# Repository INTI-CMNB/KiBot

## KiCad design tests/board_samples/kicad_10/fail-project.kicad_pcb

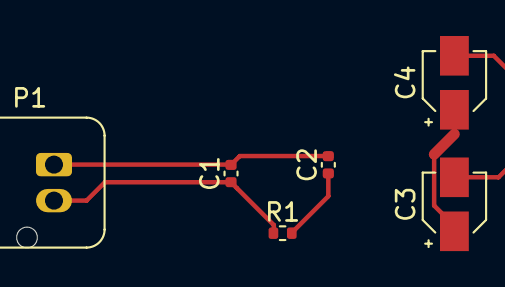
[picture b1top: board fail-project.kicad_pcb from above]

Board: 2 copper layers, 6 parts (0 on the bottom side), 5 nets.

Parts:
C1, C2: C; C_0402_1005Metric
C3, C4: CP; CP_Elec_3x5.3
P1: CONN_01X02; JST_JWPF_B02B-JWPF-SK-R_1x02_P2.00mm_Vertical
R1: R; R_0402_1005Metric

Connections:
/Power/VCC: C1.1, P1.2, R1.1
GND: C1.2, C2.2, P1.1
unnamed: C2.1, R1.2
unnamed: C3.1, C4.1
unnamed: C3.2, C4.2

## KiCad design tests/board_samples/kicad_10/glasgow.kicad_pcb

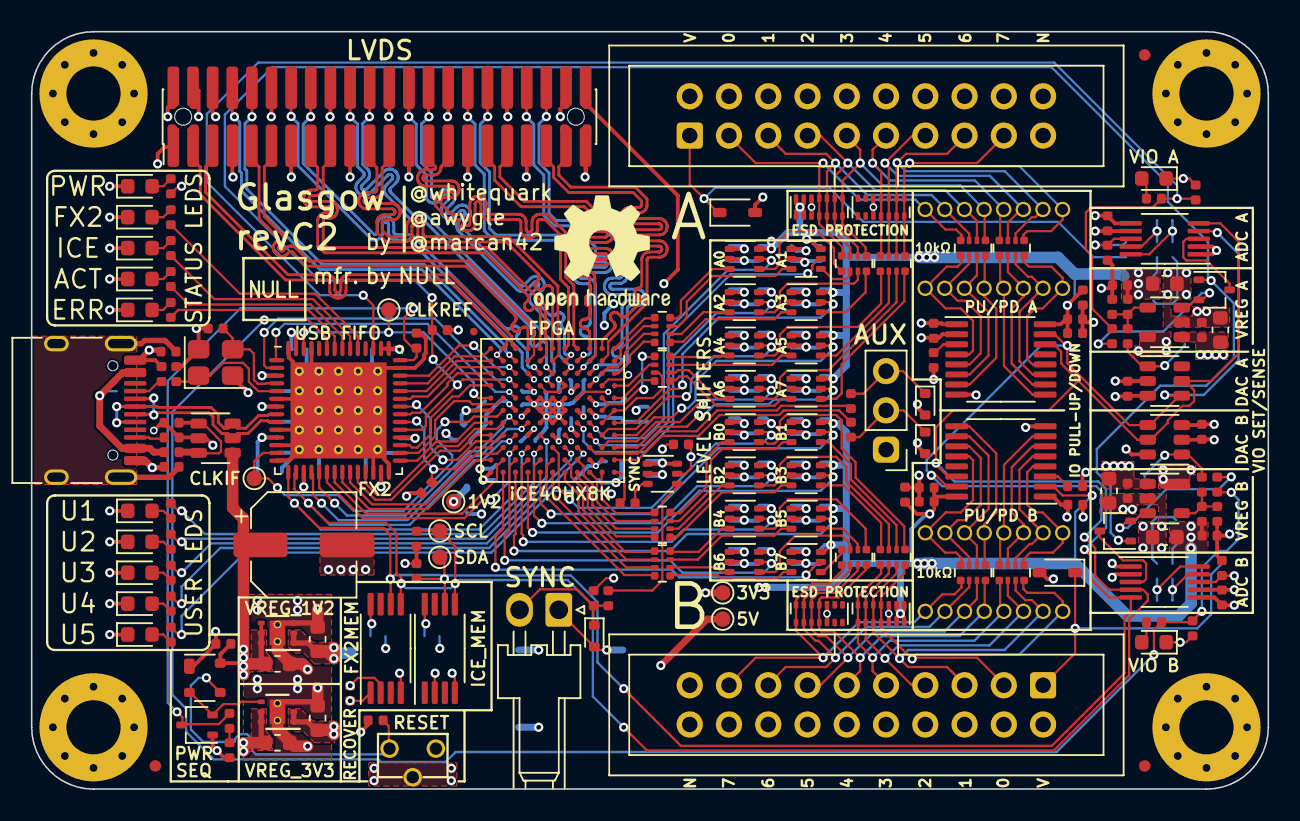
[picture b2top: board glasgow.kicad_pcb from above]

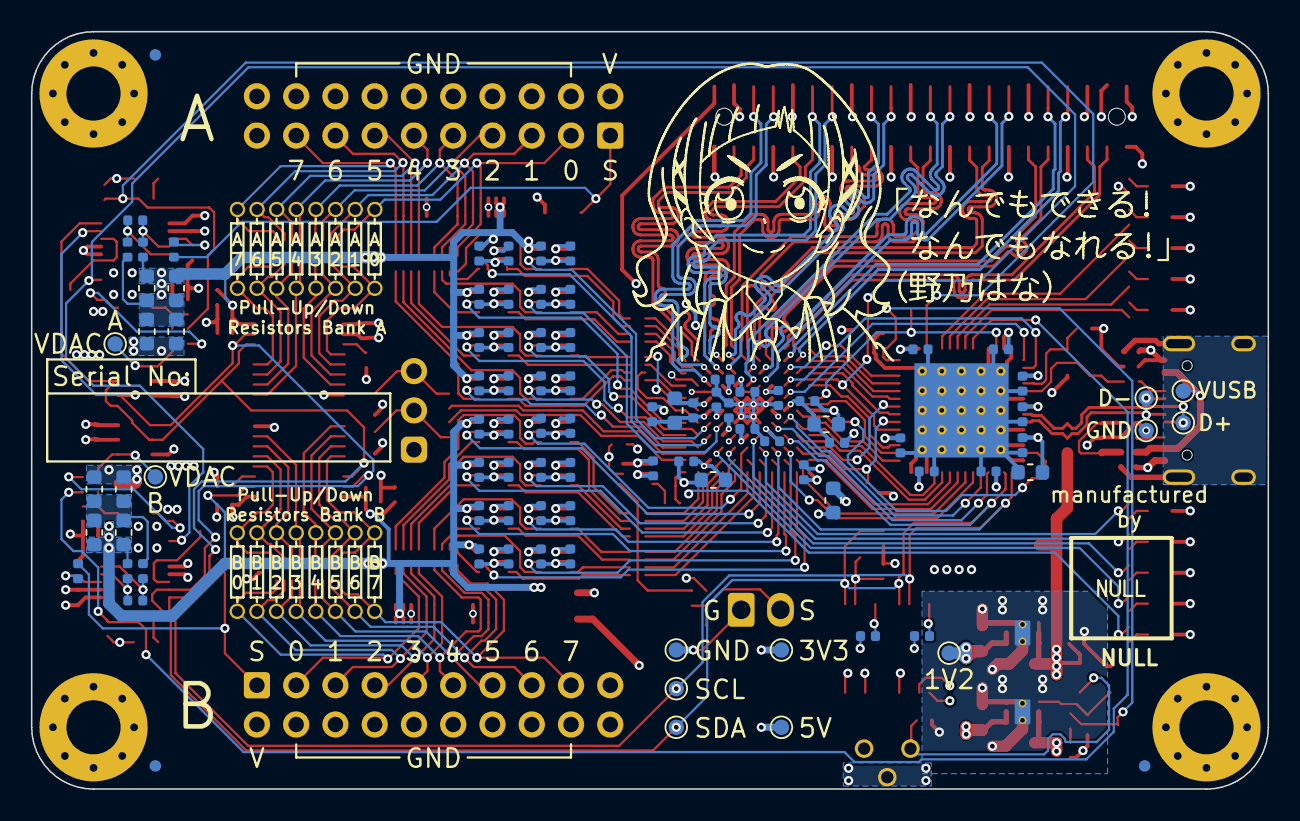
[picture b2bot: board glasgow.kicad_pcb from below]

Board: 4 copper layers, 80.0 x 49.0 mm, 264 parts (93 on the bottom side), 226 nets.

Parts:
C1, C14, C19, C26, C27, C28, C31, C53, C76, C80, C82, C83, C86: 4u7; C_0603_1608Metric
C2, C3, C4, C5, C6, C7, C8, C9, C10, C13, C15, C16, C17, C18, C20, C21, C22, C23, C24, C25, C29, C30, C32, C33, C34, C35, C36, C37, C38, C39, C40, C41, C42, C43, C44, C45, C46, C47, C48, C49, C50, C51, C52, C54, C55, C56, C57, C58, C59, C60, C61, C62, C63, C64, C65, C66, C67, C68, C69, C70, C71, C72, C73, C74, C75, C77, C78, C79, C81, C84, C85, C88, C89: u1; C_0402_1005Metric
C11, C12: 9p; C_0402_1005Metric
C87: 150u; CP_Elec_6.3x5.9
C90, C91: DNP; C_0402_1005Metric_DNP
D1, D2, D3, D14, D15: GRN; LED_0603_1608Metric
D4: YEL; LED_0603_1608Metric
D5: RED; LED_0603_1608Metric
D6, D10: BLU; LED_0603_1608Metric
D7, D9: PNK; LED_0603_1608Metric
D8: WHT; LED_0603_1608Metric
D11, D12, D13: ESD5Z5.0T1G; D_SOD-523
D16, D17: CDSOD323-T36S; D_SOD-323
D18, D19: BAT54CW; SOT-323_SC-70
D20, D21, D22, D23: SP3012-06UTG; UDFN-14_3.5x1.35mm_P0.5mm
D24: BAT54AW; SOT-323_SC-70
FB1: 600R, 0.5A; L_0402_1005Metric
FID1, FID2, FID3, FID4, FID5, FID6: Fiducial_0.75mm_Mask1.5mm
FID8: Fiducial_0.5mm_Dia_1mm_Outer
J1: USB_C_USB2.0; USB_C_Receptacle_HRO_TYPE-C-31-M-12
J2, J3: IDC-Header_2x10_P2.54mm; IDC-Header_2x10_P2.54mm_Vertical
J4: Conn_01x02; Molex_KK-254_1x02_P2.54mm_Horizontal
J5: PinHeader_2x22_P1.27mm; PinHeader_2x22_P1.27mm_Vertical__SMD
J6, J7, J8, J9: Conn_01x08; PinSocket_1x08_P1.27mm_Vertical_DNP
J10: AUX; PinHeader_1x03_P2.54mm_Vertical
MK1, MK2, MK3, MK4: Mounting_Hole_PAD; MountingHole_3.5mm_Pad_Via_CrtYd
NONO_HANA: MECHOKKU; nono_hana_lines
R1, R2, R10, R15, R41, R42, R57, R58: 2k2; R_0402_1005Metric
R3, R4, R5, R9, R17: 100k; R_0402_1005Metric
R6, R8, R50, R51: DNP; R_0603_1608Metric_DNP
R7, R56: 0R33; R_0603_1608Metric
R11, R23: 4k7; R_0402_1005Metric
R12, R13, R14, R46, R47: 20k; R_0402_1005Metric
R16, R18, R19, R20, R22, R26, R36, R37, R44, R55: 10k; R_0402_1005Metric
R21: 6k8; R_0402_1005Metric
R24, R25, R30, R54, R59, R60: 4R7; R_0402_1005Metric
R27, R33: 49k9; R_0402_1005Metric
R28, R34: 59k; R_0402_1005Metric
R29, R35: 24k3; R_0402_1005Metric
R31, R32: 100R; R_0402_1005Metric
R38, R39, R43, R45: 47R; R_0402_1005Metric
R40: DNP; R_0402_1005Metric_DNP
R48, R49: 0R15; R_0603_1608Metric
R52, R53: 5k1; R_0402_1005Metric
RN1, RN2, RN3, RN4, RN7, RN8, RN9, RN10: 33R; R_Array_Convex_4x0402
RN5, RN6, RN11, RN12: 10k; R_Array_Convex_4x0402
SW1: RST; SW_Tactile_SPST_Angled_TC-1109DE
TP1, TP8: 5V; TestPoint_Pad_D1.0mm
TP2, TP17: 1V2; TestPoint_Pad_D1.0mm
TP3, TP7, TP9: 3V3; TestPoint_Pad_D1.0mm
TP4, TP10: SDA; TestPoint_Pad_D1.0mm
TP5, TP11: SCL; TestPoint_Pad_D1.0mm
TP6: CLKREF; TestPoint_Pad_D1.0mm
TP12: GND; TestPoint_Pad_D1.0mm
TP13: VBUS; TestPoint_Pad_D1.0mm
TP14: USBGND; TestPoint_Pad_D1.0mm
TP15: USBDP; TestPoint_Pad_D1.0mm
TP16: USBDM; TestPoint_Pad_D1.0mm
TP18, TP19: VDAC; TestPoint_Pad_D1.0mm
U1: CY7C68013A-56LTX; Cypress_QFN-56-1EP_8x8mm_P0.5mm_EP6.22x6.22mm_ThermalVias
U2: CAT24M01X; TSSOP-8_4.4x3mm_P0.65mm
U3: BL24C256A-SFRC; TSSOP-8_4.4x3mm_P0.65mm
U4, U6, U9, U10, U11, U16, U17, U18, U22, U23, U24, U25, U26, U27, U28, U29, U32: SN74LVC1T45DCKR; SOT-363_SC-70-6
U5, U19: PCA6408APW; TSSOP-16_4.4x5mm_P0.65mm
U7: APX811-40UG-7; SOT-143
U8: TLV75533PDRVR; DFN-6-1EP_2x2mm_P0.65mm_EP1x1.6mm_ThermalVias
U12, U21: INA233; VSSOP-10_3x3mm_P0.5mm
U13, U20: DAC081C081CIMK; SOT-23-6
U14, U31: TPS73101DBV; SOT-23-5
U15: TPD3S014; SOT-23-6
U30: ICE40HX8K-BG121; BGA-121_9.0x9.0mm_Layout11x11_P0.8mm_Ball0.4mm_Pad0.35mm_NS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
U36: TLV73312PQDRVR; DFN-6-1EP_2x2mm_P0.65mm_EP1x1.6mm_ThermalVias
Y1: 24M; Crystal_SMD_3225-4Pin_3.2x2.5mm

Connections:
+1V2: C14.1, C18.1, C24.1, C25.1, C27.1, C77.1, R31.2, R32.2, TP2.1, TP17.1, U30.D4, U30.D8, U30.H4, U30.H8, U36.1, U36.2
+3V3: C1.1, C2.1, C3.1, C4.1, C5.1, C6.1, C7.1, C9.1, C10.1, C15.1, C17.1, C19.1, C20.1, C21.1, C22.1, C23.1, C28.1, C30.1, C32.1, C34.1, C35.1, C36.1, C37.1, C42.1, C43.1, C47.1, C48.1, C55.1, C56.1, C60.1, C61.1, C62.1, C63.1, C68.1, C69.1, C70.1, C71.1, C81.1, C84.1, C85.1, D24.1, J5.2, R1.2, R2.2, R4.1, R12.1, R17.2, R36.2, R37.2, R40.2, R44.2, TP3.1, TP9.1, U1.3, U1.7, U1.11, U1.17, U1.27, U1.32, U1.43, U1.44, U1.55, U2.2, U2.8, U3.1, U3.8, U4.1, U5.1, U6.1, U8.1, U8.2, U9.1, U10.1, U11.1, U12.2, U12.6, U13.2, U16.1, U17.1, U18.1, U19.1, U20.2, U21.6, U22.1, U23.1, U24.1, U25.1, U26.1, U27.1, U28.1, U29.1, U30.C10, U30.D6, U30.F8, U30.H6, U30.L11, U32.1, U32.6
+5V: C16.1, C26.2, C31.1, C45.1, C59.1, C82.1, C86.2, C87.1, TP1.1, TP8.1, U7.4, U8.5, U8.6, U14.1, U15.4, U31.1, U36.4, U36.5, U36.6
/A0: U1.37, U30.K3
/A1: U1.38, U30.L2
/CC1: J1.A5, R53.2
/CC2: J1.B5, R52.2
/CLKIF: TP7.1, U1.13, U30.K6
/CLKREF: TP6.1, U1.54, U30.D5, U30.L5
/D0: U1.18, U30.H7
/D1: U1.19, U30.J7
/D2: U1.20, U30.J9
/D3: U1.21, U30.K10
/D4: U1.22, U30.L10
/D5: U1.23, U30.K9
/D6: U1.24, U30.L8
/D7: U1.25, U30.K7
/ENVA: R18.1, R47.1, R55.2, U1.45
/ENVB: R19.1, R26.2, R46.1, U1.51
/FLAGA: U1.29, U30.L7
/FLAGB: U1.30, U30.K5
/FLAGC: U1.31, U30.L4
/FLAGD: U1.40, U30.J3
/FPGA_DONE: U1.36, U30.K8
/GNDPLL0: C76.2, C78.2, U30.L6
/GNDPLL1: C79.2, C80.2, U30.C5
/IO_Banks/DA0: U4.5, U30.C7
/IO_Banks/DA1: U11.5, U30.C8
/IO_Banks/DA2: U6.5, U30.D7
/IO_Banks/DA3: U16.5, U30.A7
/IO_Banks/DA4: U9.5, U30.B8
/IO_Banks/DA5: U17.5, U30.A8
/IO_Banks/DA6: U10.5, U30.B9
/IO_Banks/DA7: U18.5, U30.A9
/IO_Banks/DB0: U22.5, U30.F9
/IO_Banks/DB1: U26.5, U30.G11
/IO_Banks/DB2: U23.5, U30.G10
/IO_Banks/DB3: U27.5, U30.H11
/IO_Banks/DB4: U24.5, U30.H10
/IO_Banks/DB5: U28.5, U30.J11
/IO_Banks/DB6: U25.5, U30.J10
/IO_Banks/DB7: U29.5, U30.K11
/IO_Banks/IO_Buffer_A/ISNS_H: R8.2, R30.1, R49.1, R51.1, R56.2
/IO_Banks/IO_Buffer_A/P0: J9.1, RN11.5, U19.4
/IO_Banks/IO_Buffer_A/P1: J9.2, RN11.6, U19.5
/IO_Banks/IO_Buffer_A/P2: J9.3, RN11.7, U19.6
/IO_Banks/IO_Buffer_A/P3: J9.4, RN11.8, U19.7
/IO_Banks/IO_Buffer_A/P4: J9.5, RN12.5, U19.9
/IO_Banks/IO_Buffer_A/P5: J9.6, RN12.6, U19.10
/IO_Banks/IO_Buffer_A/P6: J9.7, RN12.7, U19.11
/IO_Banks/IO_Buffer_A/P7: J9.8, RN12.8, U19.12
/IO_Banks/IO_Buffer_A/VDAC: R33.1, TP19.1, U20.1
/IO_Banks/IO_Buffer_A/VFB: R33.2, R34.1, R35.2, U31.4
/IO_Banks/IO_Buffer_A/VIO_EN: D19.2, R55.1, U31.3
/IO_Banks/IO_Buffer_A/VSENSE: D17.1, J2.1, R60.2
/IO_Banks/IO_Buffer_A/X0: RN7.8, U4.3
/IO_Banks/IO_Buffer_A/Y0: RN9.1, U4.4
/IO_Banks/IO_Buffer_A/Y1: RN9.2, U11.4
/IO_Banks/IO_Buffer_A/Y2: RN9.3, U6.4
/IO_Banks/IO_Buffer_A/Y3: RN9.4, U16.4
/IO_Banks/IO_Buffer_A/Y4: RN10.1, U9.4
/IO_Banks/IO_Buffer_A/Y5: RN10.2, U17.4
/IO_Banks/IO_Buffer_A/Y6: RN10.3, U10.4
/IO_Banks/IO_Buffer_A/Y7: RN10.4, U18.4
/IO_Banks/IO_Buffer_A/Z0: D22.4, D22.11, J2.3, J8.1, RN9.8, RN11.4
/IO_Banks/IO_Buffer_A/Z1: D22.3, D22.12, J2.5, J8.2, RN9.7, RN11.3
/IO_Banks/IO_Buffer_A/Z2: D22.2, D22.13, J2.7, J8.3, RN9.6, RN11.2
/IO_Banks/IO_Buffer_A/Z3: D22.1, D22.14, J2.9, J8.4, RN9.5, RN11.1
/IO_Banks/IO_Buffer_A/Z4: D23.4, D23.11, J2.11, J8.5, RN10.8, RN12.4
/IO_Banks/IO_Buffer_A/Z5: D23.3, D23.12, J2.13, J8.6, RN10.7, RN12.3
/IO_Banks/IO_Buffer_A/Z6: D23.2, D23.13, J2.15, J8.7, RN10.6, RN12.2
/IO_Banks/IO_Buffer_A/Z7: D23.1, D23.14, J2.17, J8.8, RN10.5, RN12.1
/IO_Banks/IO_Buffer_B/ISNS_H: R6.2, R7.2, R24.1, R48.1, R50.1
/IO_Banks/IO_Buffer_B/P0: J7.1, RN5.5, U5.4
/IO_Banks/IO_Buffer_B/P1: J7.2, RN5.6, U5.5
/IO_Banks/IO_Buffer_B/P2: J7.3, RN5.7, U5.6
/IO_Banks/IO_Buffer_B/P3: J7.4, RN5.8, U5.7
/IO_Banks/IO_Buffer_B/P4: J7.5, RN6.5, U5.9
/IO_Banks/IO_Buffer_B/P5: J7.6, RN6.6, U5.10
/IO_Banks/IO_Buffer_B/P6: J7.7, RN6.7, U5.11
/IO_Banks/IO_Buffer_B/P7: J7.8, RN6.8, U5.12
/IO_Banks/IO_Buffer_B/VDAC: R27.1, TP18.1, U13.1
/IO_Banks/IO_Buffer_B/VFB: R27.2, R28.1, R29.2, U14.4
/IO_Banks/IO_Buffer_B/VIO_EN: D18.2, R26.1, U14.3
/IO_Banks/IO_Buffer_B/VSENSE: D16.1, J3.1, R59.2
/IO_Banks/IO_Buffer_B/X0: RN1.8, U22.3
/IO_Banks/IO_Buffer_B/Y0: RN3.1, U22.4
/IO_Banks/IO_Buffer_B/Y1: RN3.2, U26.4
/IO_Banks/IO_Buffer_B/Y2: RN3.3, U23.4
/IO_Banks/IO_Buffer_B/Y3: RN3.4, U27.4
/IO_Banks/IO_Buffer_B/Y4: RN4.1, U24.4
/IO_Banks/IO_Buffer_B/Y5: RN4.2, U28.4
/IO_Banks/IO_Buffer_B/Y6: RN4.3, U25.4
/IO_Banks/IO_Buffer_B/Y7: RN4.4, U29.4
/IO_Banks/IO_Buffer_B/Z0: D20.4, D20.11, J3.3, J6.1, RN3.8, RN5.4
/IO_Banks/IO_Buffer_B/Z1: D20.3, D20.12, J3.5, J6.2, RN3.7, RN5.3
/IO_Banks/IO_Buffer_B/Z2: D20.2, D20.13, J3.7, J6.3, RN3.6, RN5.2
/IO_Banks/IO_Buffer_B/Z3: D20.1, D20.14, J3.9, J6.4, RN3.5, RN5.1
/IO_Banks/IO_Buffer_B/Z4: D21.4, D21.11, J3.11, J6.5, RN4.8, RN6.4
/IO_Banks/IO_Buffer_B/Z5: D21.3, D21.12, J3.13, J6.6, RN4.7, RN6.3
/IO_Banks/IO_Buffer_B/Z6: D21.2, D21.13, J3.15, J6.7, RN4.6, RN6.2
/IO_Banks/IO_Buffer_B/Z7: D21.1, D21.14, J3.17, J6.8, RN4.5, RN6.1
/IO_Banks/QA0: RN7.1, U30.A1
/IO_Banks/QA1: RN7.2, U30.A2
/IO_Banks/QA2: RN7.3, U30.B3
/IO_Banks/QA3: RN7.4, U30.A3
/IO_Banks/QA4: RN8.1, U30.B5, U30.B6
/IO_Banks/QA5: RN8.2, U30.A4
/IO_Banks/QA6: RN8.3, U30.A6, U30.B7
/IO_Banks/QA7: RN8.4, U30.A5
/IO_Banks/QB0: RN1.1, U30.B11
/IO_Banks/QB1: RN1.2, U30.C11
/IO_Banks/QB2: RN1.3, U30.D10
/IO_Banks/QB3: RN1.4, U30.D11
/IO_Banks/QB4: RN2.1, U30.E10
/IO_Banks/QB5: RN2.2, U30.E11
/IO_Banks/QB6: RN2.3, U30.F11
/IO_Banks/QB7: RN2.4, U30.F10
/IO_Banks/U1: R11.1, U30.G9
/IO_Banks/U2: R20.1, U30.G8
/IO_Banks/U3: R21.1, U30.E9
/IO_Banks/U4: R22.1, U30.D9
/IO_Banks/U5: R23.1, U30.E8
/IO_Banks/VIOA: C38.1, C39.1, C40.1, C41.1, C49.1, C50.1, C51.1, C52.1, C54.1, C57.1, C83.1, D22.6, D22.7, D22.8, D22.9, J2.2, R34.2, R42.2, R49.2, R51.2, R54.1, R58.2, U4.6, U6.6, U9.6, U10.6, U11.6, U16.6, U17.6, U18.6, U19.16
/IO_Banks/VIOB: C29.1, C46.1, C53.1, C64.1, C65.1, C66.1, C67.1, C72.1, C73.1, C74.1, C75.1, D20.6, D20.7, D20.8, D20.9, J3.2, R25.1, R28.2, R41.2, R48.2, R50.2, R57.2, U5.2, U5.16, U22.6, U23.6, U24.6, U25.6, U26.6, U27.6, U28.6, U29.6
/IO_Banks/VIO_AUX: C33.1, J5.44, U30.E4, U30.G4
/IO_Banks/Z0_N: J5.41, U30.B2
/IO_Banks/Z0_P: J5.39, U30.B1
/IO_Banks/Z1_N: J5.38, U30.C3
/IO_Banks/Z1_P: J5.40, U30.C4
/IO_Banks/Z2_N: J5.33, U30.C1
/IO_Banks/Z2_P: J5.35, U30.C2
/IO_Banks/Z3_N: J5.29, U30.D1
/IO_Banks/Z3_P: J5.27, U30.E1
/IO_Banks/Z4_N: J5.34, U30.D3
/IO_Banks/Z4_P: J5.32, U30.D2
/IO_Banks/Z5_N: J5.26, U30.E3
/IO_Banks/Z5_P: J5.28, U30.E2
/IO_Banks/Z6_N: J5.23, U30.F2
/IO_Banks/Z6_P: J5.21, U30.F1
/IO_Banks/Z7_N: J5.20, U30.F3
/IO_Banks/Z7_P: J5.22, U30.F4
/IO_Banks/Z8_N: J5.17, U30.G2
/IO_Banks/Z8_P: J5.15, U30.G1
/IO_Banks/Z9_N: J5.14, U30.H3
/IO_Banks/Z9_P: J5.16, U30.G3
/IO_Banks/Z10_N: J5.11, U30.H2
/IO_Banks/Z10_P: J5.9, U30.H1
/IO_Banks/Z11_N: J5.3, U30.K1
/IO_Banks/Z11_P: J5.5, U30.J1
/IO_Banks/Z12_N: J5.10, U30.J2
/IO_Banks/Z12_P: J5.8, U30.K2
/IO_Banks/~SYNC: D11.1, J4.2, R38.1, R44.1
/LED_ACT: R15.1, U1.49
/LED_CY: R13.1, U1.47
/LED_ERR: R16.1, U1.50
/LED_FPGA: R14.1, U1.48
/OE: U1.35, U30.L3
/PKTEND: U1.39, U30.L1
/RD: U1.1, U30.J5
/SCL: R2.1, TP5.1, TP11.1, U1.15, U2.6, U3.6, U5.14, U12.5, U13.5, U19.14, U20.5, U21.5, U30.H9
/SDA: R1.1, TP4.1, TP10.1, U1.16, U2.5, U3.5, U5.15, U12.4, U13.4, U19.15, U20.4, U21.4, U30.J8
/SHLD: C13.1, J1.S1, R3.1
/USB_N: J1.A7, J1.B7, TP16.1, U1.9, U15.5
/USB_P: J1.A6, J1.B6, TP15.1, U1.8, U15.6
/VCCPLL0: C76.1, C78.1, R31.1, U30.J6
/VCCPLL1: C79.1, C80.1, R32.1, U30.C6
/VUSB: C8.1, FB1.2, U15.1, U15.3
/WR: U1.2, U30.J4
/XTALIN: C12.1, U1.5, Y1.1
/XTALOUT: C11.1, U1.4, Y1.3
/xVBUS: FB1.1, J1.A4, J1.A9, J1.B4, J1.B9, TP13.1
/~ALERT: D18.1, D19.1, R17.1, U1.33, U30.K4
/~CY_RESET: C88.1, D24.3, R5.2, U1.42
/~FPGA_RESET: R9.2, U1.34, U30.L9
/~MR: C89.1, SW1.2, U7.3
GND: C1.2, C2.2, C3.2, C4.2, C5.2, C6.2, C7.2, C8.2, C9.2, C10.2, C11.2, C12.2, C13.2, C14.2, C15.2, C16.2, C17.2, C18.2, C19.2, C20.2, C21.2, C22.2, C23.2, C24.2, C25.2, C26.1, C27.2, C28.2, C29.2, C30.2, C31.2, C32.2, C33.2, C34.2, C35.2, C36.2, C37.2, C38.2, C39.2, C40.2, C41.2, C42.2, C43.2, C45.2, C46.2, C47.2, C48.2, C49.2, C50.2, C51.2, C52.2, C53.2, C54.2, C55.2, C56.2, C57.2, C59.2, C60.2, C61.2, C62.2, C63.2, C64.2, C65.2, C66.2, C67.2, C68.2, C69.2, C70.2, C71.2, C72.2, C73.2, C74.2, C75.2, C77.2, C81.2, C82.2, C83.2, C84.2, C85.2, C86.1, C87.2, C88.2, C89.2, C90.1, C91.1, D1.1, D2.1, D3.1, D4.1, D5.1, D6.1, D7.1, D8.1, D9.1, D10.1, D11.2, D12.2, D13.2, D14.1, D15.1, D16.2, D17.2, D20.5, D20.10, D21.5, D21.10, D22.5, D22.10, D23.5, D23.10, J1.A1, J1.A12, J1.B1, J1.B12, J2.4, J2.6, J2.8, J2.10, J2.12, J2.14, J2.16, J2.18, J3.4, J3.6, J3.8, J3.10, J3.12, J3.14, J3.16, J3.18, J4.1, J5.1, J5.4, J5.6, J5.7, J5.12, J5.13, J5.18, J5.19, J5.24, J5.25, J5.30, J5.31, J5.36, J5.37, J5.42, J5.43, J10.1, MK1.1, MK2.1, MK3.1, MK4.1, R3.2, R9.1, R10.2, R18.2, R19.2, R29.1, R35.1, R41.1, R42.1, R52.1, R53.1, R57.1, R58.1, SW1.1, TP12.1, TP14.1, U1.6, U1.10, U1.12, U1.14, U1.26, U1.28, U1.41, U1.53, U1.56, U1.57, U2.4, U3.4, U4.2, U5.8, U6.2, U7.1, U8.3, U8.7, U9.2, U10.2, U11.2, U12.1, U12.7, U13.3, U13.6, U14.2, U15.2, U16.2, U17.2, U18.2, U19.2, U19.8, U20.3, U21.1, U21.2, U21.7, U22.2, U23.2, U24.2, U25.2, U26.2, U27.2, U28.2, U29.2, U30.E5, U30.E6, U30.E7, U30.F5, U30.F6, U30.F7, U30.G5, U30.G6, U30.G7, U30.H5, U31.2, U32.2, U36.3, U36.7, Y1.2, Y1.4
unnamed: C44.1, R25.2, U12.9
unnamed: C44.2, R24.2, U12.10
unnamed: C58.1, R54.2, U21.9
unnamed: C58.2, R30.2, U21.10
unnamed: C90.2, R59.1, U12.8
unnamed: C91.2, R60.1, U21.8
unnamed: D1.2, R12.2
unnamed: D2.2, R13.2
unnamed: D3.2, R14.2
unnamed: D4.2, R15.2
unnamed: D5.2, R16.2
unnamed: D6.2, R11.2
unnamed: D7.2, R20.2
unnamed: D8.2, R21.2
unnamed: D9.2, R22.2
unnamed: D10.2, R23.2
unnamed: D12.1, J10.2, R39.1
unnamed: D13.1, J10.3, R43.1
unnamed: D14.2, R46.2
unnamed: D15.2, R47.2
unnamed: D18.3, U12.3
unnamed: D19.3, U21.3
unnamed: D24.2, U7.2, U8.4
unnamed: R4.2, R5.1
unnamed: R6.1, R7.1, U14.5
unnamed: R10.1, U30.B4, U32.5
unnamed: R36.1, U5.3
unnamed: R37.1, U19.3
unnamed: R38.2, U32.4
unnamed: R39.2, U30.A10
unnamed: R40.1, U3.2
unnamed: R43.2, U30.C9
unnamed: R45.1, U32.3
unnamed: R45.2, U30.A11
unnamed: R8.1, R56.1, U31.5
unnamed: RN1.5, U27.3
unnamed: RN1.6, U23.3
unnamed: RN1.7, U26.3
unnamed: RN2.5, U29.3
unnamed: RN2.6, U25.3
unnamed: RN2.7, U28.3
unnamed: RN2.8, U24.3
unnamed: RN7.5, U16.3
unnamed: RN7.6, U6.3
unnamed: RN7.7, U11.3
unnamed: RN8.5, U18.3
unnamed: RN8.6, U10.3
unnamed: RN8.7, U17.3
unnamed: RN8.8, U9.3
